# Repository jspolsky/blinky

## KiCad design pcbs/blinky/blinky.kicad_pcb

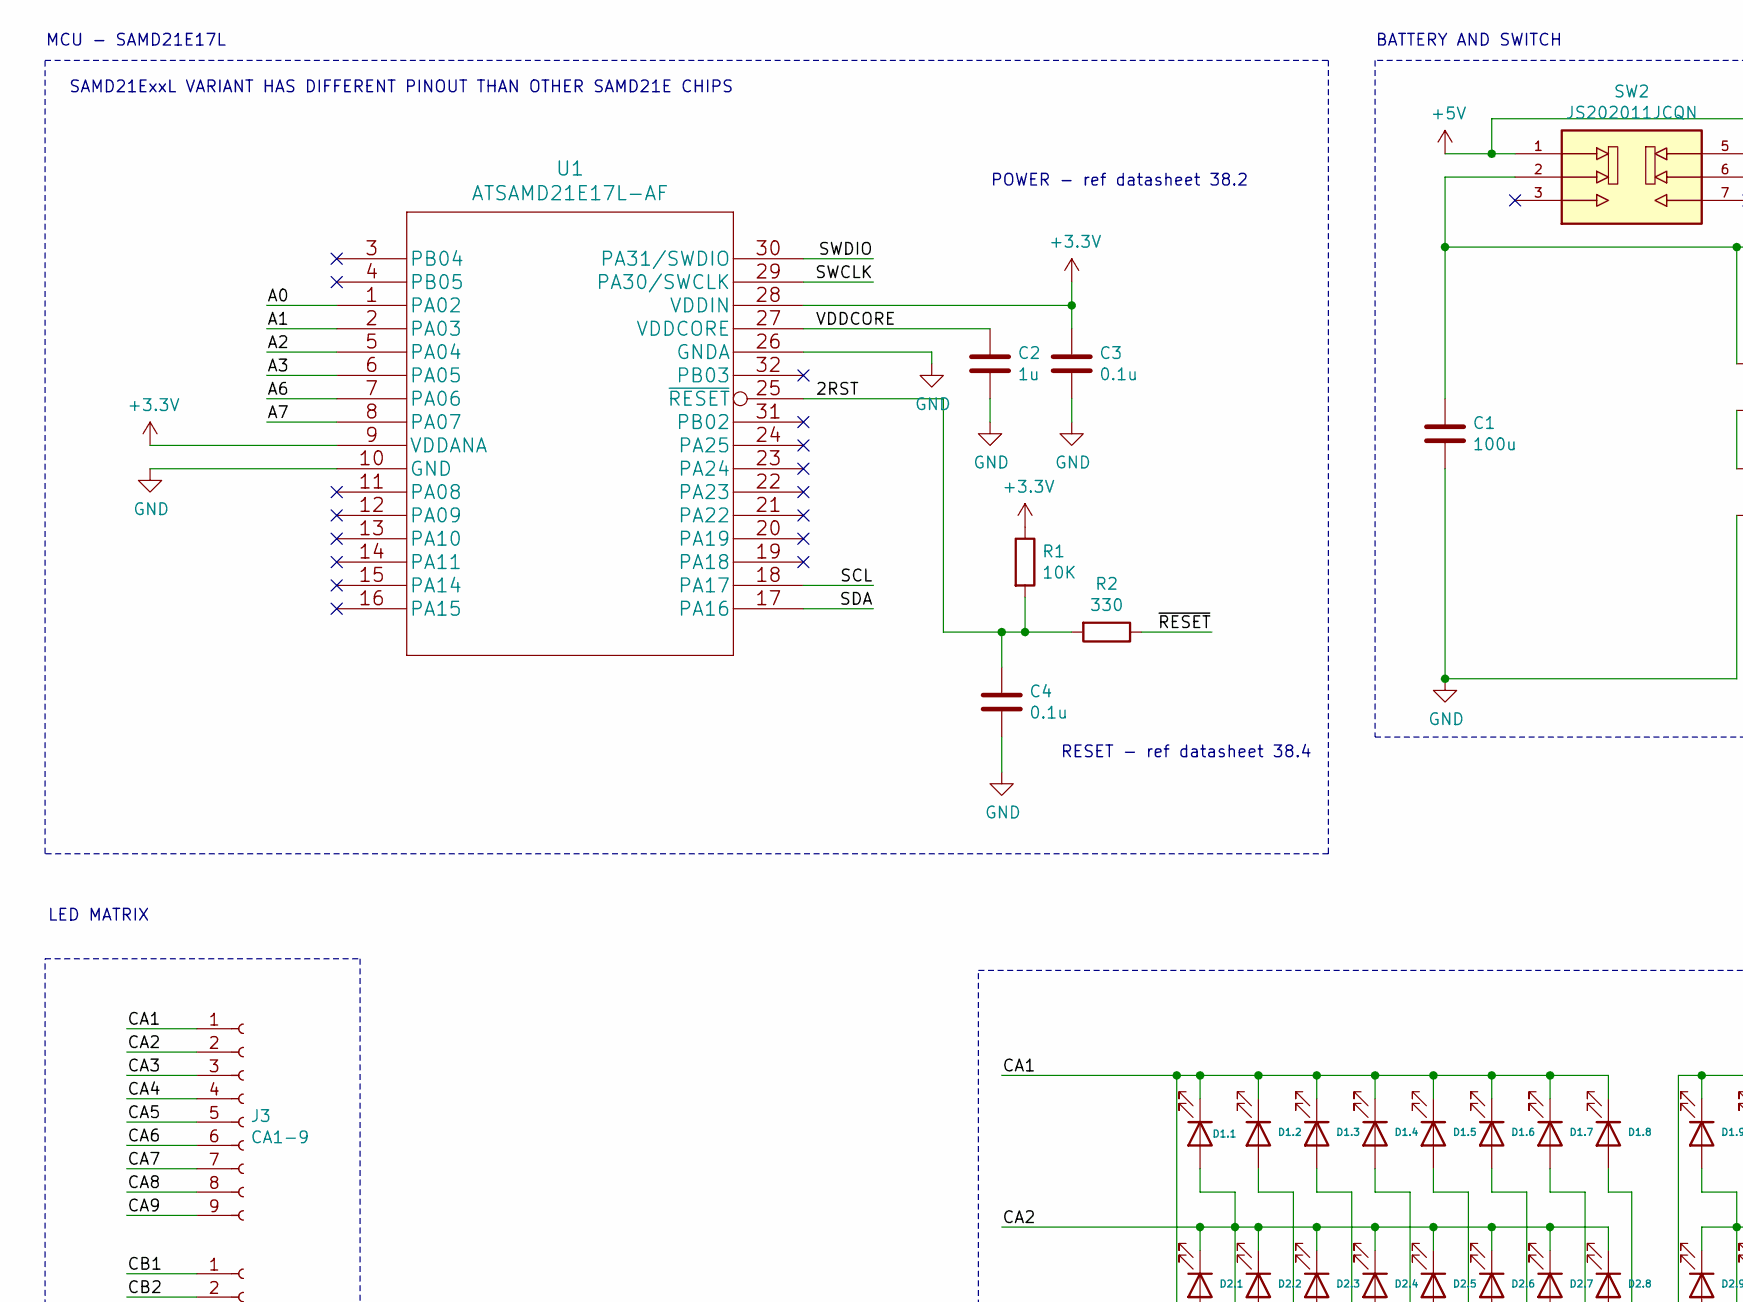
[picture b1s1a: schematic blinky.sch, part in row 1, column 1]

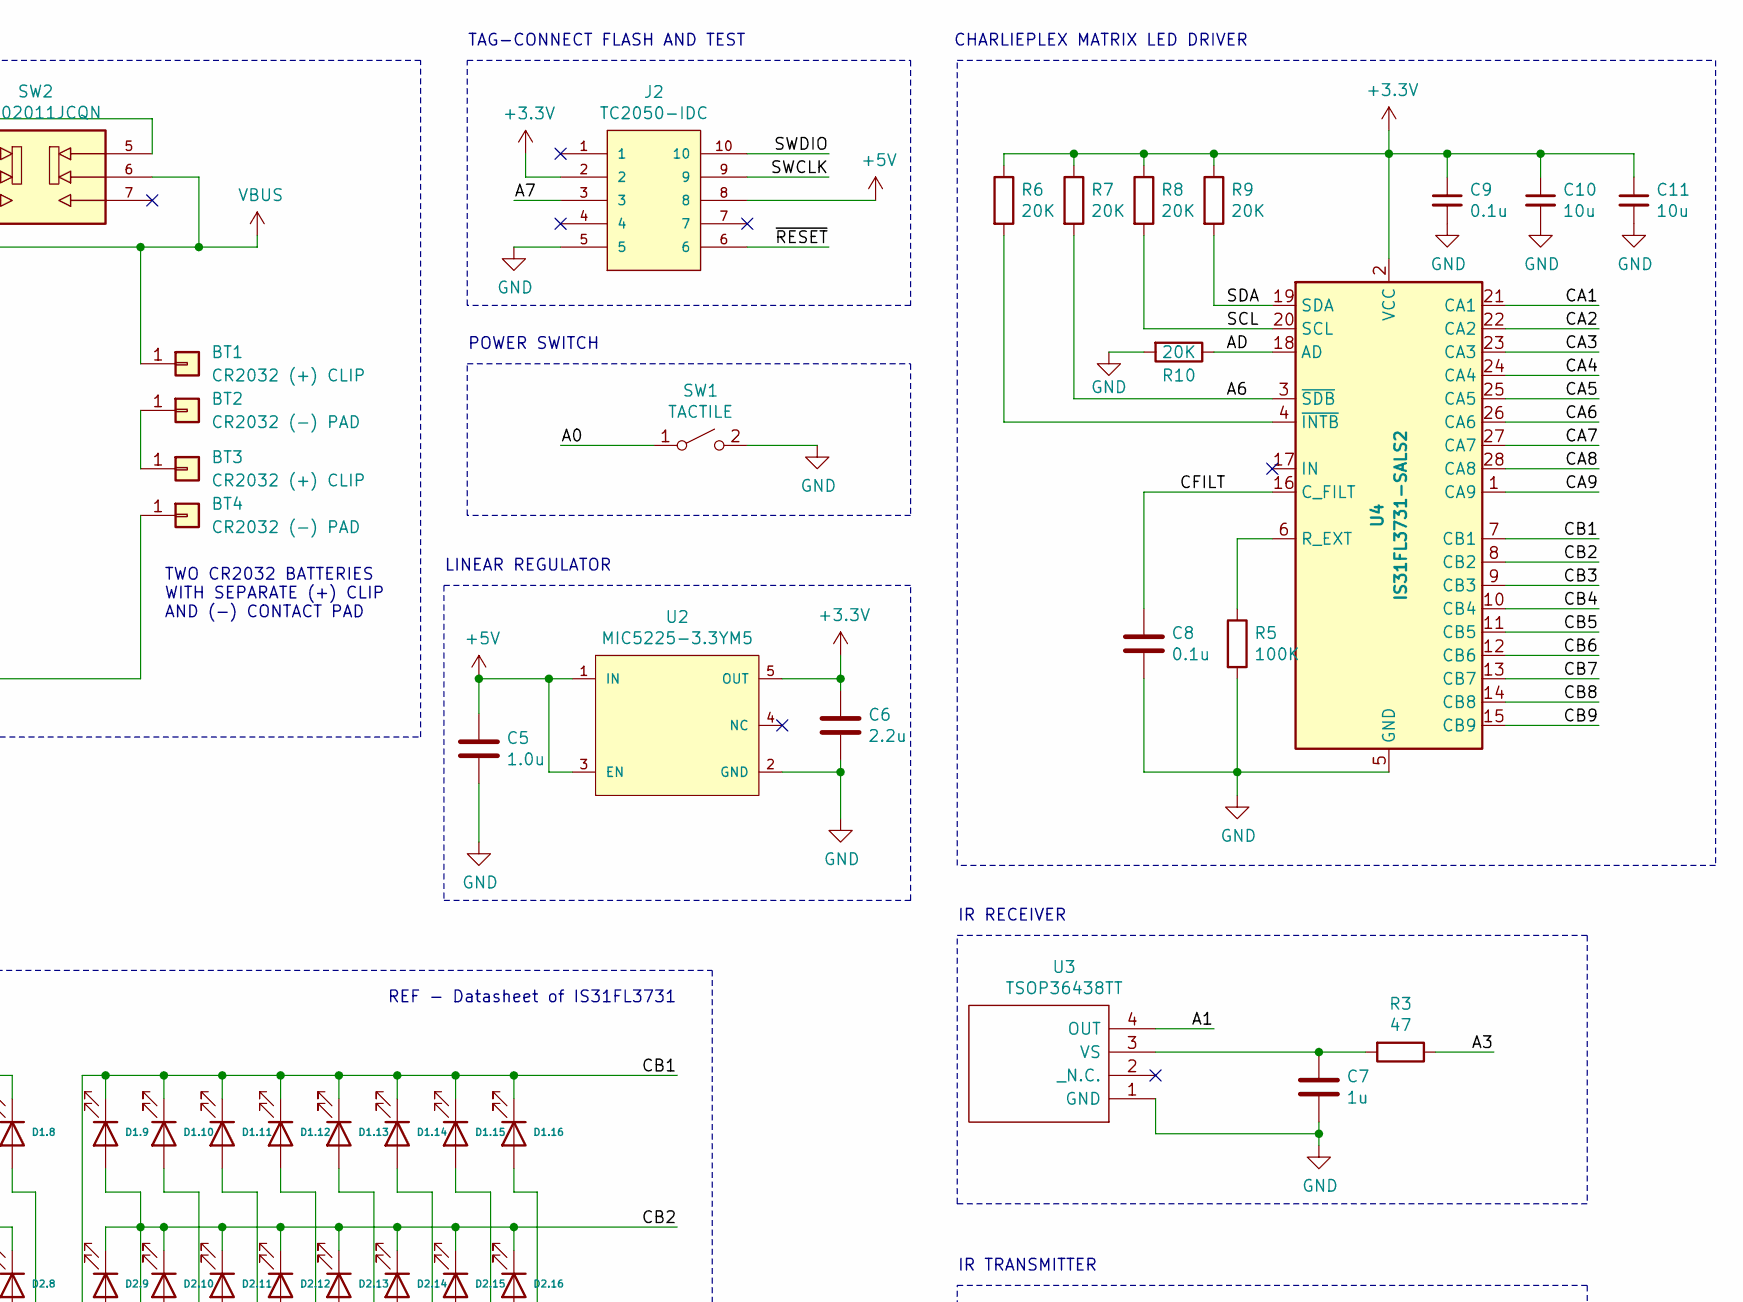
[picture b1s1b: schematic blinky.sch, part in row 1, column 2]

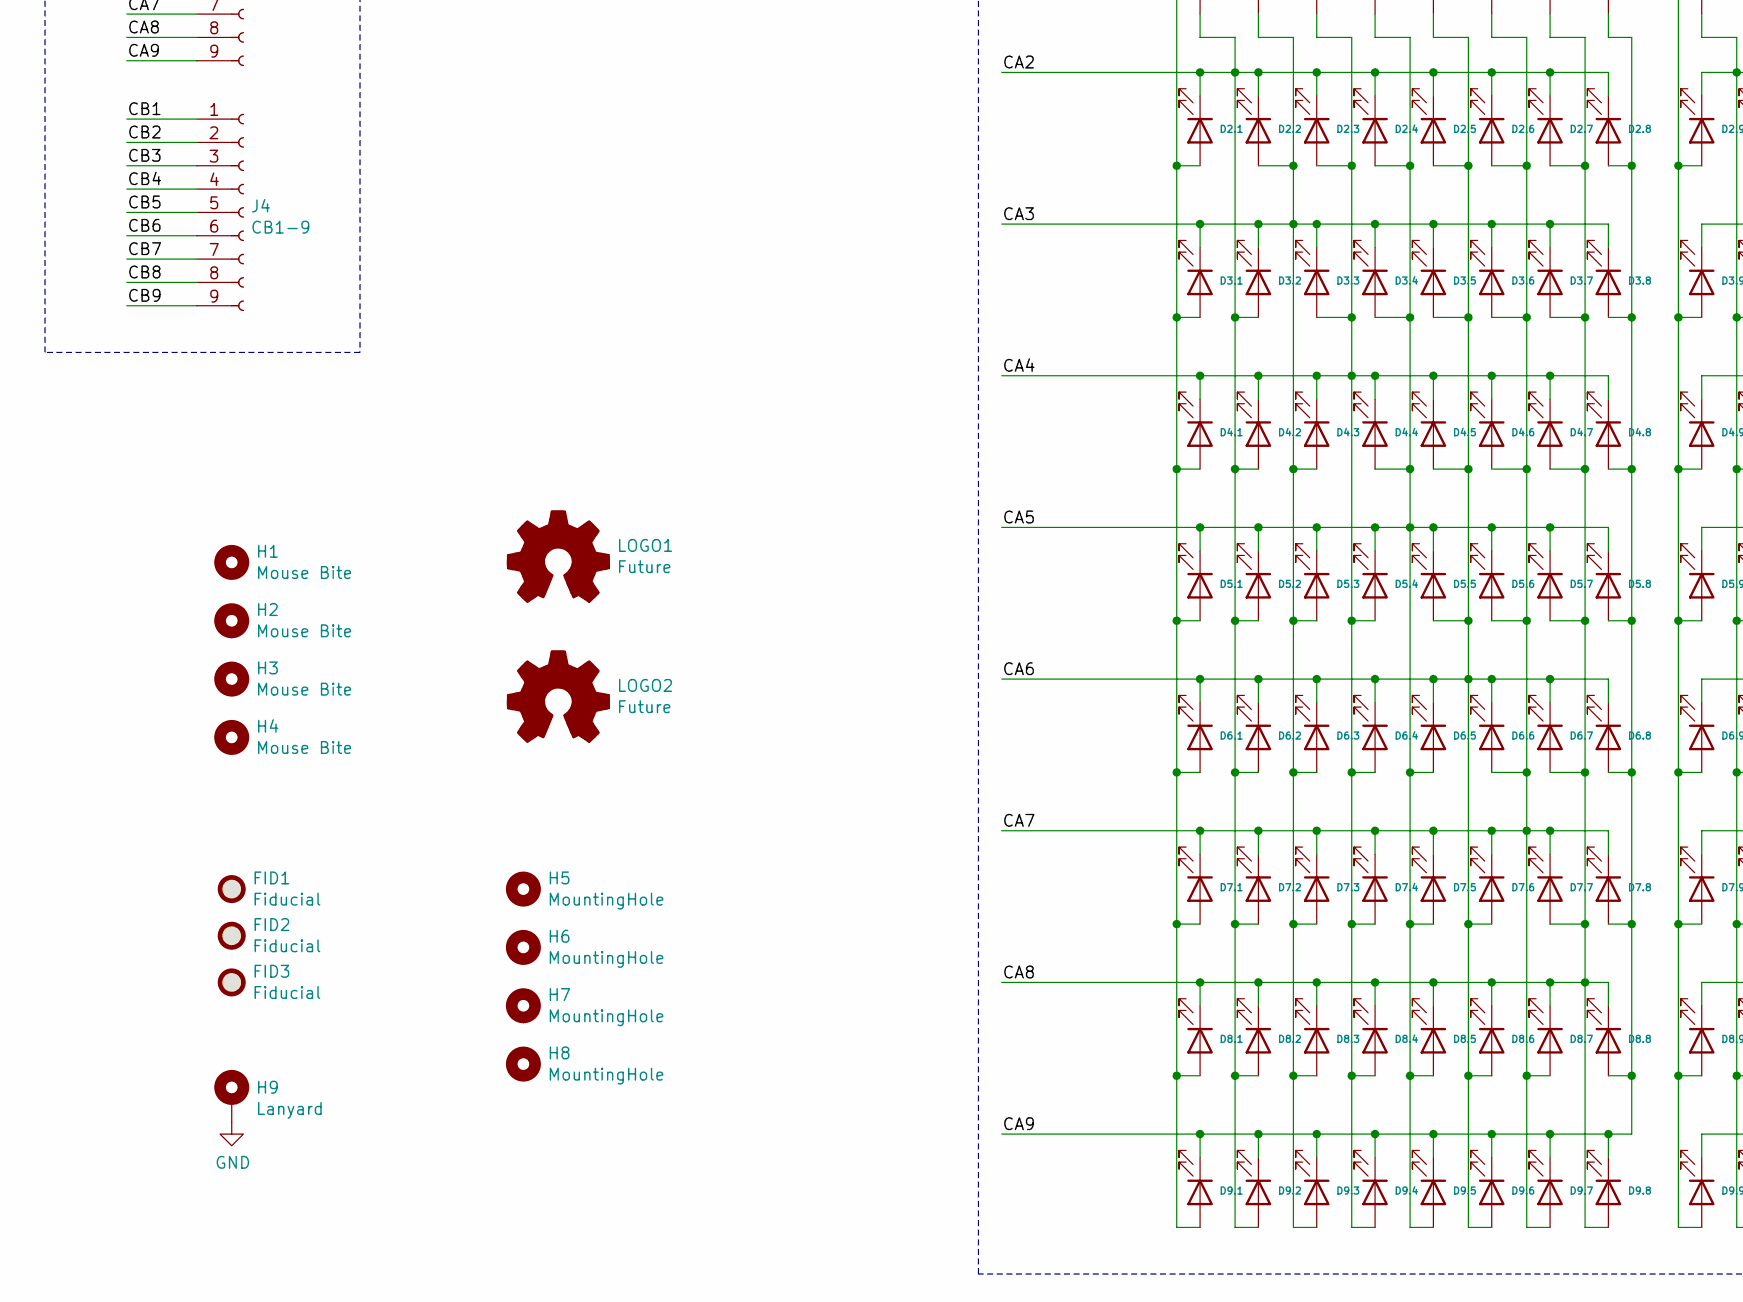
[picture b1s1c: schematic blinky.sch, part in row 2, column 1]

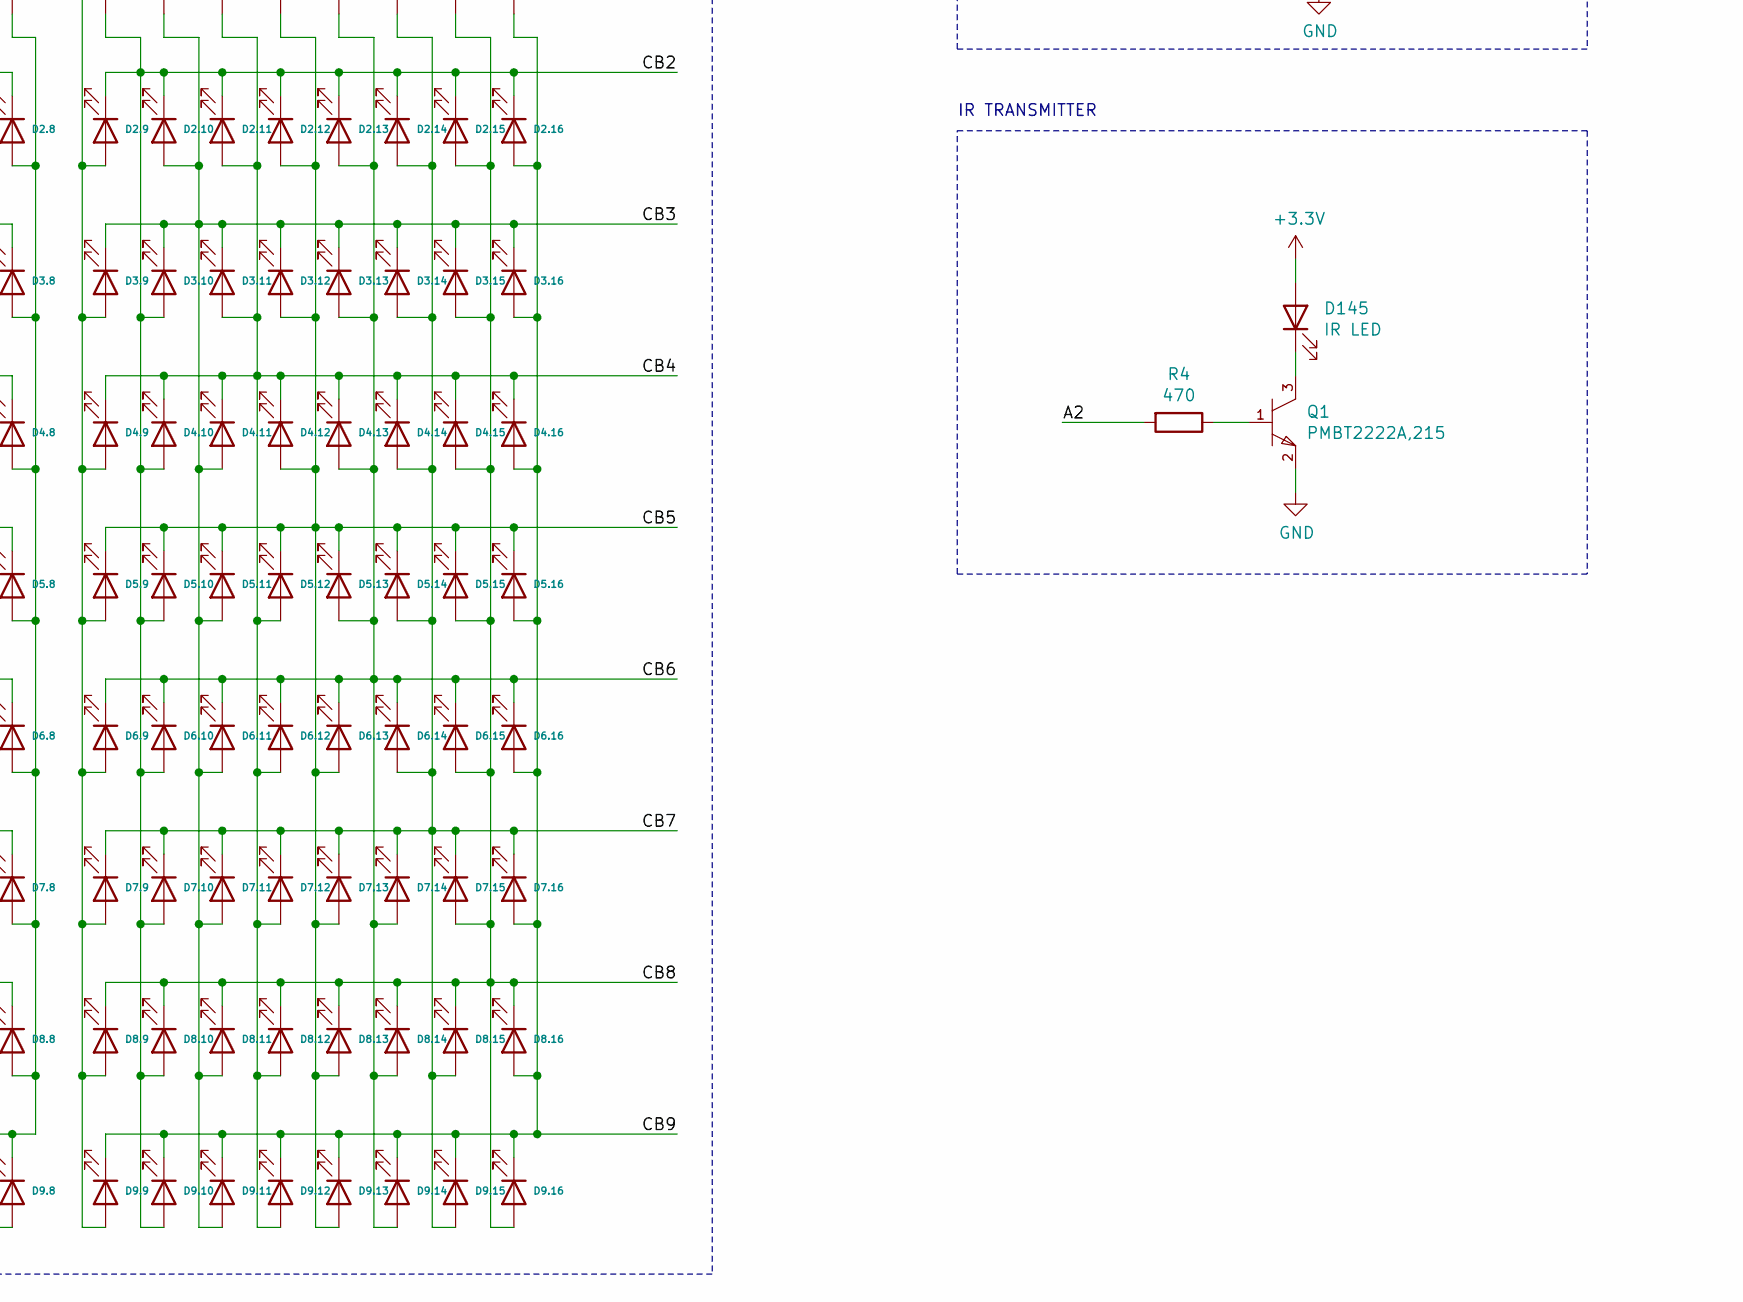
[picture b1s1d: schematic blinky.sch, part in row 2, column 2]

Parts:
BT1, BT3: CR2032 (+) CLIP; BatteryHolder_Keystone_3034_Pos_Clip; part number 3034
BT2, BT4: CR2032 (-) PAD; Keystone_2992_Negative_Contact_Pad
C1: 100u; C_1206_3216Metric
C2, C7: 1u; C_0603_1608Metric
C3, C4, C8, C9: 0.1u; C_0603_1608Metric
C5: 1.0u; C_0603_1608Metric
C6: 2.2u; C_0603_1608Metric
C10, C11: 10u; C_0603_1608Metric
D1.1, D1.2, D1.3, D1.4, D1.5, D1.6, D1.7, D1.8, D1.9, D1.10, D1.11, D1.12, D1.13, D1.14, D1.15, D1.16, D2.1, D2.2, D2.3, D2.4, D2.5, D2.6, D2.7, D2.8, D2.9, D2.10, D2.11, D2.12, D2.13, D2.14, D2.15, D2.16, D3.1, D3.2, D3.3, D3.4, D3.5, D3.6, D3.7, D3.8, D3.9, D3.10, D3.11, D3.12, D3.13, D3.14, D3.15, D3.16, D4.1, D4.2, D4.3, D4.4, D4.5, D4.6, D4.7, D4.8, D4.9, D4.10, D4.11, D4.12, D4.13, D4.14, D4.15, D4.16, D5.1, D5.2, D5.3, D5.4, D5.5, D5.6, D5.7, D5.8, D5.9, D5.10, D5.11, D5.12, D5.13, D5.14, D5.15, D5.16, D6.1, D6.2, D6.3, D6.4, D6.5, D6.6, D6.7, D6.8, D6.9, D6.10, D6.11, D6.12, D6.13, D6.14, D6.15, D6.16, D7.1, D7.2, D7.3, D7.4, D7.5, D7.6, D7.7, D7.8, D7.9, D7.10, D7.11, D7.12, D7.13, D7.14, D7.15, D7.16, D8.1, D8.2, D8.3, D8.4, D8.5, D8.6, D8.7, D8.8, D8.9, D8.10, D8.11, D8.12, D8.13, D8.14, D8.15, D8.16, D9.1, D9.2, D9.3, D9.4, D9.5, D9.6, D9.7, D9.8, D9.9, D9.10, D9.11, D9.12, D9.13, D9.14, D9.15, D9.16: LED; LED_0603_For_Blinky
D145: IR LED; LED_0805_2012Metric; part number APT2012F3C
FID1, FID2, FID3: Fiducial; Fiducial_1mm_Mask3mm
H1, H2, H3, H4: Mouse Bite; Mouse_Bite_For_Clipper
H5, H6, H7, H8: MountingHole; JCLPCB_Tooling_Hole
H9: Lanyard; MountingHole_2.5mm_Pad_Via
J2: TC2050-IDC; TAG-CONNECT_TC2050-IDC; PARTREV A
J3: CA1-9; PinHeader_1x09_P2.54mm_Vertical
J4: CB1-9; PinHeader_1x09_P2.54mm_Vertical
LOGO1: Future; logo-future
LOGO2: Future; logo-turtles
Q1: PMBT2222A,215; NXP-TO-236AB-0-0-0; mouser part number 771-PMBT2222A-T/R; digikey description TRANS NPN 40V 0.6A SOT23
R1: 10K; R_0603_1608Metric
R2: 330; R_0603_1608Metric
R3: 47; R_0603_1608Metric
R4: 470; R_0603_1608Metric
R5: 100K; R_0603_1608Metric
R6, R7, R8, R9, R10: 20K; R_0603_1608Metric
SW1: TACTILE; TL9320AF400QG; part number TL9320AF 400QG
SW2: JS202011JCQN; CK-JS202011JCQN; PARTREV 11 Nov 19
U1: ATSAMD21E17L-AF; ATSAMD21E17_32Pin_TQFP
U2: MIC5225-3.3YM5; MIC5225-SOT23-5LD; dropout voltage 310mV; output voltage 3.3V; mouser part number 998-MIC5225-3.3YM5TR; digikey description IC REG LINEAR 3.3V 150MA SOT23-5
U3: TSOP36438TT; Manufacturer_Part_Number TSOP36438TT; Mouser Part Number 78-TSOP36438TT
U4: IS31FL3731-SALS2; SSOP-28_5.3x10.2mm_P0.65mm; part number IS31FL3731-SALS2

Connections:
+3V3: C3.1, C6.1, C9.1, C10.1, C11.1, D145.2 (A), J2.2, R1.1, R6.1, R7.1, R8.1, R9.1, U1.9 (VDDANA), U1.28 (VDDIN), U2.5 (OUT), U4.2 (VCC)
+5V: C5.1, J2.8, SW2.1, SW2.5, U2.1 (IN), U2.3 (EN)
/2RST: C4.1, R1.2, R2.2, U1.25 (~RESET)
/A0: SW1.1 (A), U1.1 (PA02)
/A1: U1.2 (PA03), U3.4 (OUT)
/A2: R4.2, U1.5 (PA04)
/A3: R3.1, U1.6 (PA05)
/A6: R7.2, U1.7 (PA06), U4.3 (~SDB)
/A7: J2.3, U1.8 (PA07)
/AD: R10.1, U4.18 (AD)
/CA1: D1.1.1 (K), D1.2.1 (K), D1.3.1 (K), D1.4.1 (K), D1.5.1 (K), D1.6.1 (K), D1.7.1 (K), D1.8.1 (K), D2.1.2 (A), D3.1.2 (A), D4.1.2 (A), D5.1.2 (A), D6.1.2 (A), D7.1.2 (A), D8.1.2 (A), D9.1.2 (A), J3.1, U4.21 (CA1)
/CA2: D1.1.2 (A), D2.1.1 (K), D2.2.1 (K), D2.3.1 (K), D2.4.1 (K), D2.5.1 (K), D2.6.1 (K), D2.7.1 (K), D2.8.1 (K), D3.2.2 (A), D4.2.2 (A), D5.2.2 (A), D6.2.2 (A), D7.2.2 (A), D8.2.2 (A), D9.2.2 (A), J3.2, U4.22 (CA2)
/CA3: D1.2.2 (A), D2.2.2 (A), D3.1.1 (K), D3.2.1 (K), D3.3.1 (K), D3.4.1 (K), D3.5.1 (K), D3.6.1 (K), D3.7.1 (K), D3.8.1 (K), D4.3.2 (A), D5.3.2 (A), D6.3.2 (A), D7.3.2 (A), D8.3.2 (A), D9.3.2 (A), J3.3, U4.23 (CA3)
/CA4: D1.3.2 (A), D2.3.2 (A), D3.3.2 (A), D4.1.1 (K), D4.2.1 (K), D4.3.1 (K), D4.4.1 (K), D4.5.1 (K), D4.6.1 (K), D4.7.1 (K), D4.8.1 (K), D5.4.2 (A), D6.4.2 (A), D7.4.2 (A), D8.4.2 (A), D9.4.2 (A), J3.4, U4.24 (CA4)
/CA5: D1.4.2 (A), D2.4.2 (A), D3.4.2 (A), D4.4.2 (A), D5.1.1 (K), D5.2.1 (K), D5.3.1 (K), D5.4.1 (K), D5.5.1 (K), D5.6.1 (K), D5.7.1 (K), D5.8.1 (K), D6.5.2 (A), D7.5.2 (A), D8.5.2 (A), D9.5.2 (A), J3.5, U4.25 (CA5)
/CA6: D1.5.2 (A), D2.5.2 (A), D3.5.2 (A), D4.5.2 (A), D5.5.2 (A), D6.1.1 (K), D6.2.1 (K), D6.3.1 (K), D6.4.1 (K), D6.5.1 (K), D6.6.1 (K), D6.7.1 (K), D6.8.1 (K), D7.6.2 (A), D8.6.2 (A), D9.6.2 (A), J3.6, U4.26 (CA6)
/CA7: D1.6.2 (A), D2.6.2 (A), D3.6.2 (A), D4.6.2 (A), D5.6.2 (A), D6.6.2 (A), D7.1.1 (K), D7.2.1 (K), D7.3.1 (K), D7.4.1 (K), D7.5.1 (K), D7.6.1 (K), D7.7.1 (K), D7.8.1 (K), D8.7.2 (A), D9.7.2 (A), J3.7, U4.27 (CA7)
/CA8: D1.7.2 (A), D2.7.2 (A), D3.7.2 (A), D4.7.2 (A), D5.7.2 (A), D6.7.2 (A), D7.7.2 (A), D8.1.1 (K), D8.2.1 (K), D8.3.1 (K), D8.4.1 (K), D8.5.1 (K), D8.6.1 (K), D8.7.1 (K), D8.8.1 (K), D9.8.2 (A), J3.8, U4.28 (CA8)
/CA9: D1.8.2 (A), D2.8.2 (A), D3.8.2 (A), D4.8.2 (A), D5.8.2 (A), D6.8.2 (A), D7.8.2 (A), D8.8.2 (A), D9.1.1 (K), D9.2.1 (K), D9.3.1 (K), D9.4.1 (K), D9.5.1 (K), D9.6.1 (K), D9.7.1 (K), D9.8.1 (K), J3.9, U4.1 (CA9)
/CB1: D1.9.1 (K), D1.10.1 (K), D1.11.1 (K), D1.12.1 (K), D1.13.1 (K), D1.14.1 (K), D1.15.1 (K), D1.16.1 (K), D2.9.2 (A), D3.9.2 (A), D4.9.2 (A), D5.9.2 (A), D6.9.2 (A), D7.9.2 (A), D8.9.2 (A), D9.9.2 (A), J4.1, U4.7 (CB1)
/CB2: D1.9.2 (A), D2.9.1 (K), D2.10.1 (K), D2.11.1 (K), D2.12.1 (K), D2.13.1 (K), D2.14.1 (K), D2.15.1 (K), D2.16.1 (K), D3.10.2 (A), D4.10.2 (A), D5.10.2 (A), D6.10.2 (A), D7.10.2 (A), D8.10.2 (A), D9.10.2 (A), J4.2, U4.8 (CB2)
/CB3: D1.10.2 (A), D2.10.2 (A), D3.9.1 (K), D3.10.1 (K), D3.11.1 (K), D3.12.1 (K), D3.13.1 (K), D3.14.1 (K), D3.15.1 (K), D3.16.1 (K), D4.11.2 (A), D5.11.2 (A), D6.11.2 (A), D7.11.2 (A), D8.11.2 (A), D9.11.2 (A), J4.3, U4.9 (CB3)
/CB4: D1.11.2 (A), D2.11.2 (A), D3.11.2 (A), D4.9.1 (K), D4.10.1 (K), D4.11.1 (K), D4.12.1 (K), D4.13.1 (K), D4.14.1 (K), D4.15.1 (K), D4.16.1 (K), D5.12.2 (A), D6.12.2 (A), D7.12.2 (A), D8.12.2 (A), D9.12.2 (A), J4.4, U4.10 (CB4)
/CB5: D1.12.2 (A), D2.12.2 (A), D3.12.2 (A), D4.12.2 (A), D5.9.1 (K), D5.10.1 (K), D5.11.1 (K), D5.12.1 (K), D5.13.1 (K), D5.14.1 (K), D5.15.1 (K), D5.16.1 (K), D6.13.2 (A), D7.13.2 (A), D8.13.2 (A), D9.13.2 (A), J4.5, U4.11 (CB5)
/CB6: D1.13.2 (A), D2.13.2 (A), D3.13.2 (A), D4.13.2 (A), D5.13.2 (A), D6.9.1 (K), D6.10.1 (K), D6.11.1 (K), D6.12.1 (K), D6.13.1 (K), D6.14.1 (K), D6.15.1 (K), D6.16.1 (K), D7.14.2 (A), D8.14.2 (A), D9.14.2 (A), J4.6, U4.12 (CB6)
/CB7: D1.14.2 (A), D2.14.2 (A), D3.14.2 (A), D4.14.2 (A), D5.14.2 (A), D6.14.2 (A), D7.9.1 (K), D7.10.1 (K), D7.11.1 (K), D7.12.1 (K), D7.13.1 (K), D7.14.1 (K), D7.15.1 (K), D7.16.1 (K), D8.15.2 (A), D9.15.2 (A), J4.7, U4.13 (CB7)
/CB8: D1.15.2 (A), D2.15.2 (A), D3.15.2 (A), D4.15.2 (A), D5.15.2 (A), D6.15.2 (A), D7.15.2 (A), D8.9.1 (K), D8.10.1 (K), D8.11.1 (K), D8.12.1 (K), D8.13.1 (K), D8.14.1 (K), D8.15.1 (K), D8.16.1 (K), D9.16.2 (A), J4.8, U4.14 (CB8)
/CB9: D1.16.2 (A), D2.16.2 (A), D3.16.2 (A), D4.16.2 (A), D5.16.2 (A), D6.16.2 (A), D7.16.2 (A), D8.16.2 (A), D9.9.1 (K), D9.10.1 (K), D9.11.1 (K), D9.12.1 (K), D9.13.1 (K), D9.14.1 (K), D9.15.1 (K), D9.16.1 (K), J4.9, U4.15 (CB9)
/CFILT: C8.1, U4.16 (C_FILT)
/SCL: R8.2, U1.18 (PA17), U4.20 (SCL)
/SDA: R9.2, U1.17 (PA16), U4.19 (SDA)
/SWCLK: J2.9, U1.29 (PA30/SWCLK)
/SWDIO: J2.10, U1.30 (PA31/SWDIO)
/VDDCORE: C2.1, U1.27 (VDDCORE)
/~RESET: J2.6, R2.1
GND: BT4.1, C1.2, C2.2, C3.2, C4.2, C5.2, C6.2, C7.2, C8.2, C9.2, C10.2, C11.2, H9.1, J2.5, Q1.2 (emitter), R5.2, R10.2, SW1.2 (B), U1.10 (GND), U1.26 (GNDA), U2.2 (GND), U3.1 (GND), U4.5 (GND)
unnamed: BT2.1, BT3.1
unnamed: C7.1, R3.2, U3.3 (VS)
unnamed: D145.1 (K), Q1.3 (collector)
unnamed: Q1.1 (base), R4.1
unnamed: R5.1, U4.6 (R_EXT)
unnamed: R6.2, U4.4 (~INTB)
VBUS: BT1.1, C1.1, SW2.2, SW2.6

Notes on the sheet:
MCU - SAMD21E17L
RESET - ref datasheet 38.4
POWER - ref datasheet 38.2
LINEAR REGULATOR
BATTERY AND SWITCH
POWER SWITCH
CHARLIEPLEX MATRIX LED DRIVER
IR TRANSMITTER
IR RECEIVER
LED MATRIX
REF - Datasheet of IS31FL3731
SAMD21ExxL VARIANT HAS DIFFERENT PINOUT THAN OTHER SAMD21E CHIPS
TAG-CONNECT FLASH AND TEST
TWO CR2032 BATTERIES WITH SEPARATE (+) CLIP AND (-) CONTACT PAD

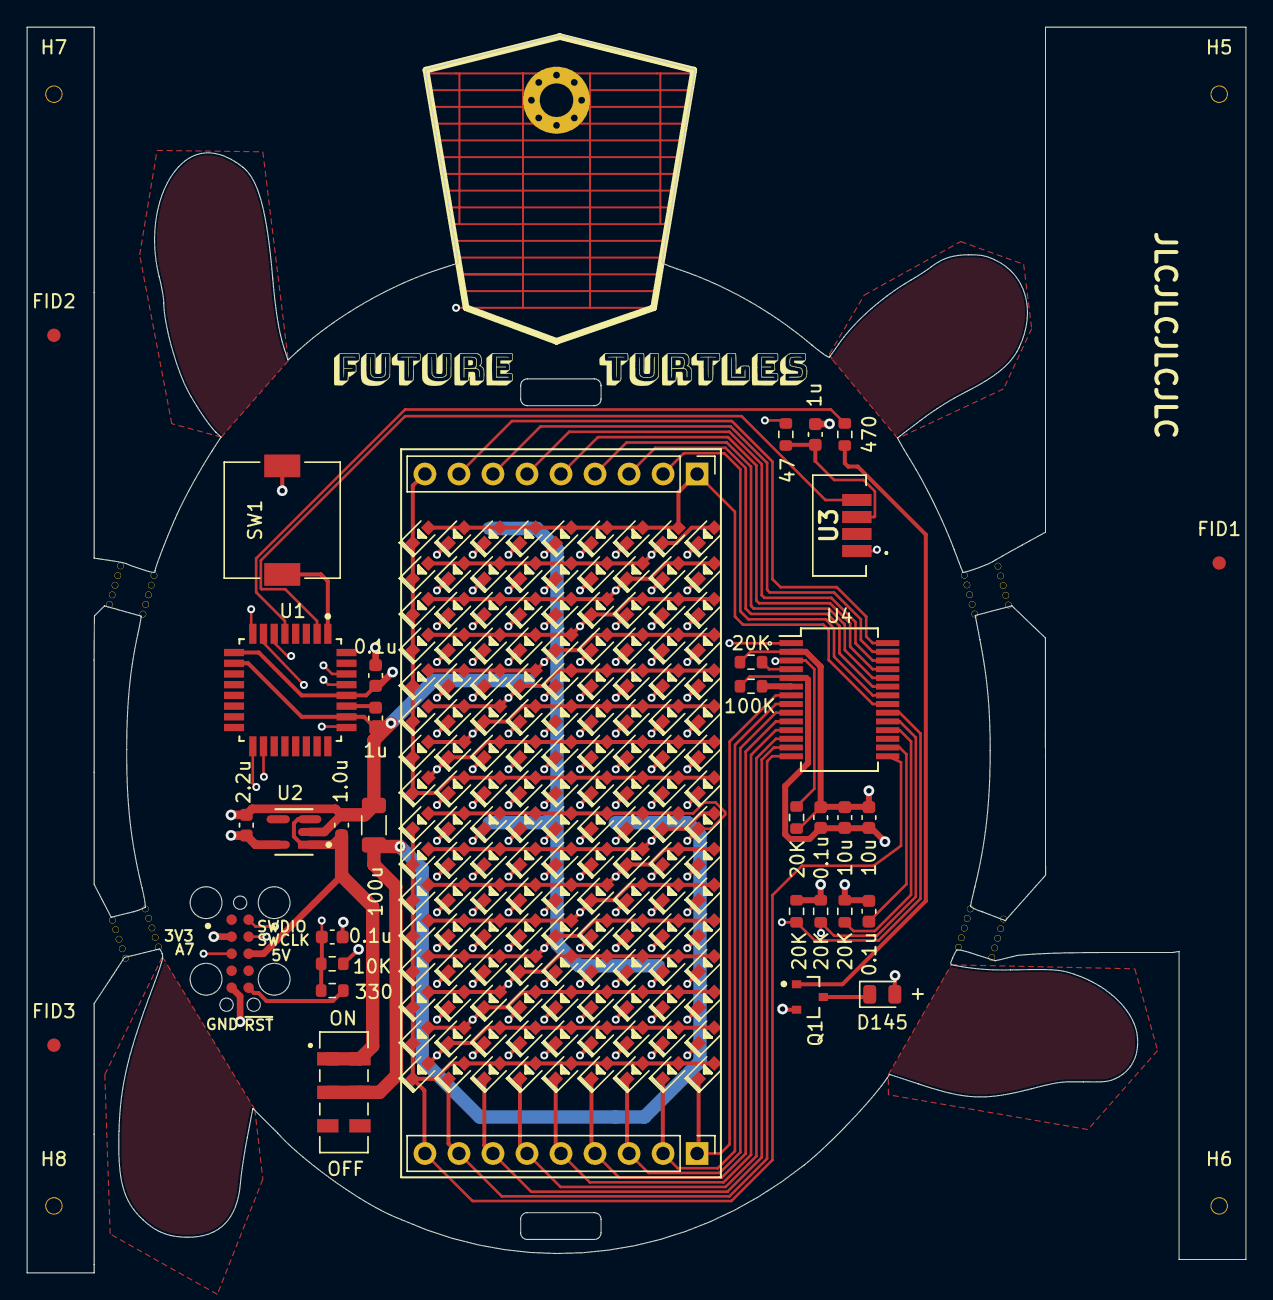
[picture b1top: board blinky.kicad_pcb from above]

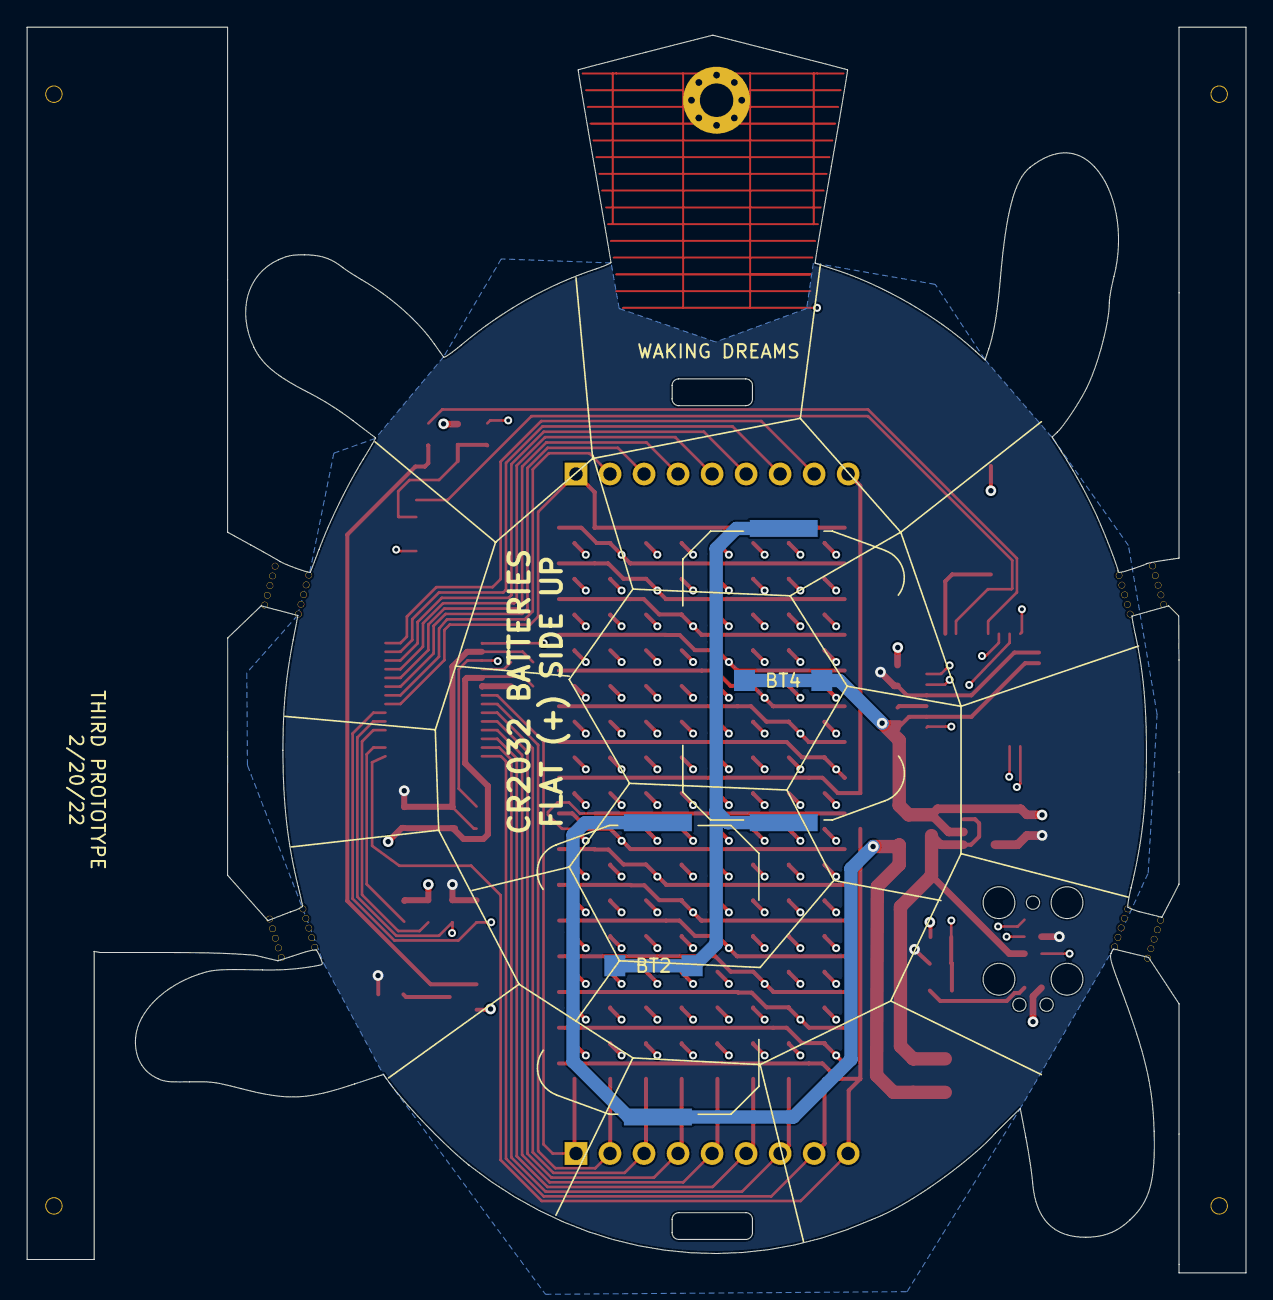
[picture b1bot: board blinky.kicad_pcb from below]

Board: 4 copper layers, 91.0 x 93.0 mm, 194 parts (4 on the bottom side), 43 nets.

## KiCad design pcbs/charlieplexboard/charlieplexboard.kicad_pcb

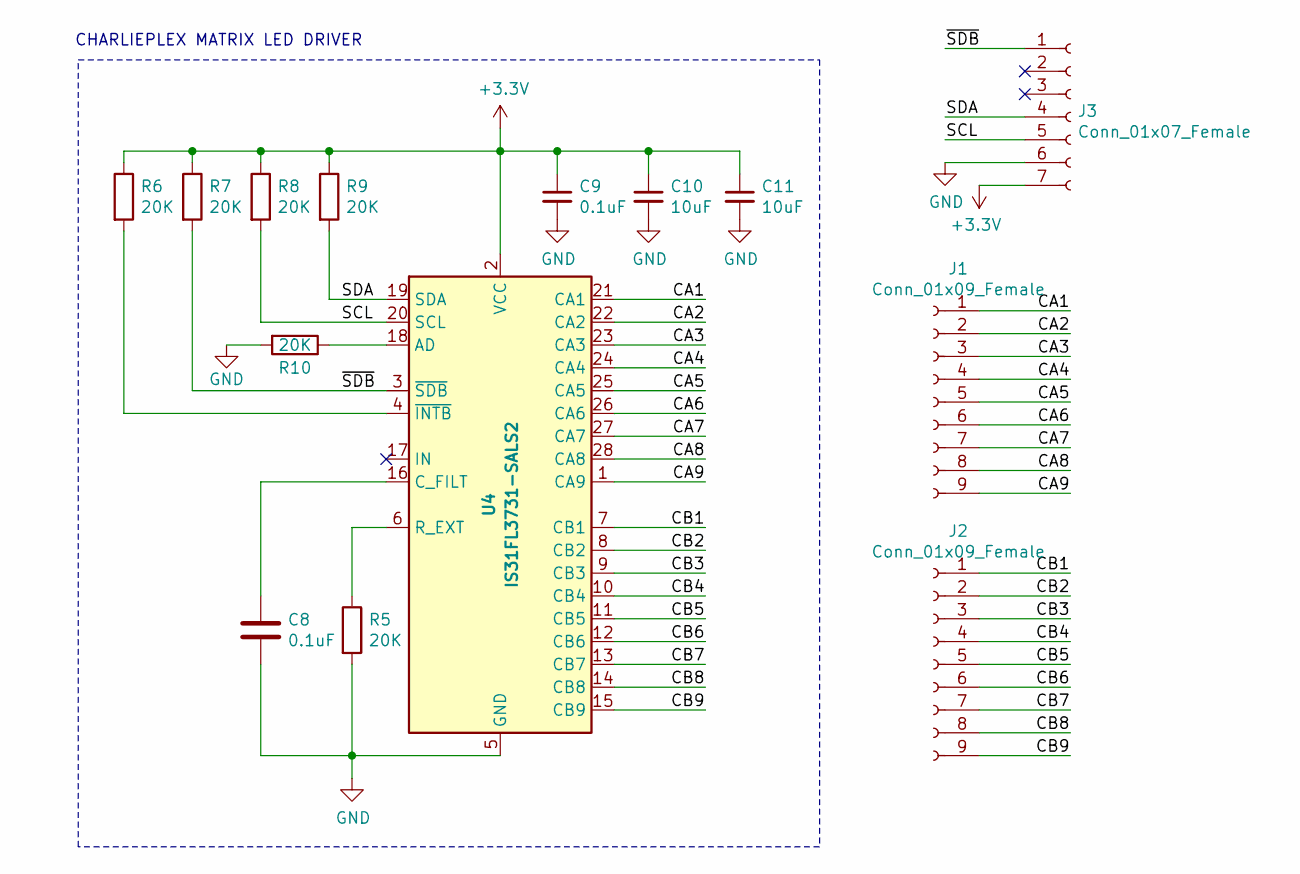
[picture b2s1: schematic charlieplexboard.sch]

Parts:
C8, C9: 0.1uF; C_0603_1608Metric
C10, C11: 10uF; C_0603_1608Metric
J1, J2: Conn_01x09_Female; PinSocket_1x09_P2.54mm_Vertical
J3: Conn_01x07_Female; PinHeader_1x07_P2.54mm_Vertical
R5, R6, R7, R8, R9, R10: 20K; R_0603_1608Metric
U4: IS31FL3731-SALS2; SSOP-28_5.3x10.2mm_P0.65mm; part number IS31FL3731-SALS2

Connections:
+3V3: C9.1, C10.1, C11.1, J3.7, R6.1, R7.1, R8.1, R9.1, U4.2 (VCC)
/CA1: J1.1, U4.21 (CA1)
/CA2: J1.2, U4.22 (CA2)
/CA3: J1.3, U4.23 (CA3)
/CA4: J1.4, U4.24 (CA4)
/CA5: J1.5, U4.25 (CA5)
/CA6: J1.6, U4.26 (CA6)
/CA7: J1.7, U4.27 (CA7)
/CA8: J1.8, U4.28 (CA8)
/CA9: J1.9, U4.1 (CA9)
/CB1: J2.1, U4.7 (CB1)
/CB2: J2.2, U4.8 (CB2)
/CB3: J2.3, U4.9 (CB3)
/CB4: J2.4, U4.10 (CB4)
/CB5: J2.5, U4.11 (CB5)
/CB6: J2.6, U4.12 (CB6)
/CB7: J2.7, U4.13 (CB7)
/CB8: J2.8, U4.14 (CB8)
/CB9: J2.9, U4.15 (CB9)
/SCL: J3.5, R8.2, U4.20 (SCL)
/SDA: J3.4, R9.2, U4.19 (SDA)
/~SDB: J3.1, R7.2, U4.3 (~SDB)
GND: C8.2, C9.2, C10.2, C11.2, J3.6, R5.2, R10.2, U4.5 (GND)
unnamed: C8.1, U4.16 (C_FILT)
unnamed: R5.1, U4.6 (R_EXT)
unnamed: R6.2, U4.4 (~INTB)
unnamed: R10.1, U4.18 (AD)

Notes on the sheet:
CHARLIEPLEX MATRIX LED DRIVER

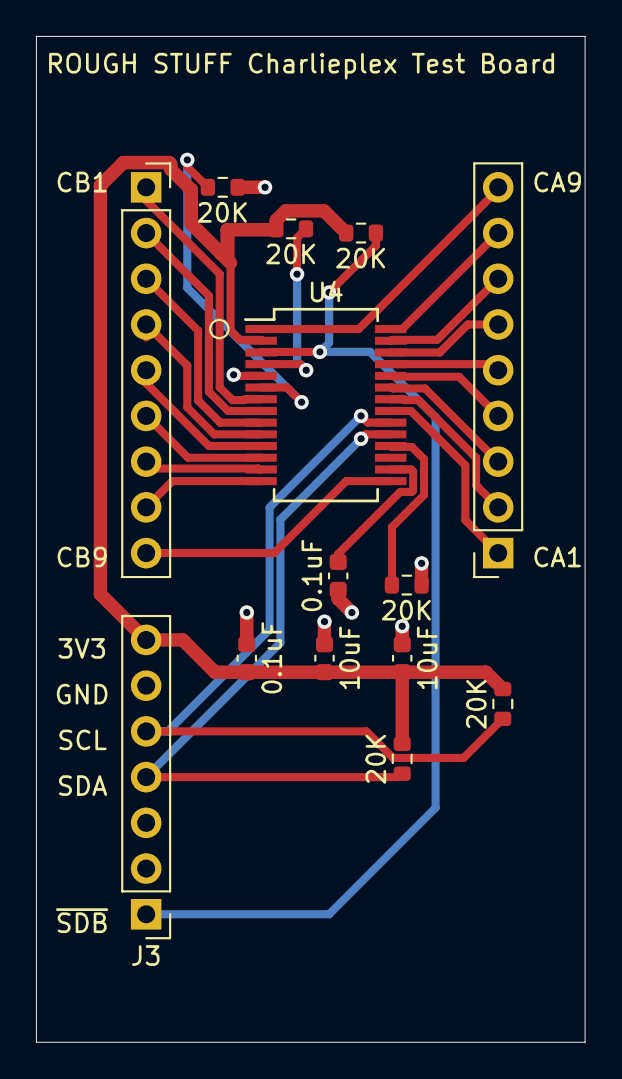
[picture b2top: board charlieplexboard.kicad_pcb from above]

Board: 2 copper layers, 30.5 x 55.9 mm, 14 parts (0 on the bottom side), 27 nets.

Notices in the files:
parts and their libraries:
Copyright 2021 Accelerated Designs. All rights reserved.
